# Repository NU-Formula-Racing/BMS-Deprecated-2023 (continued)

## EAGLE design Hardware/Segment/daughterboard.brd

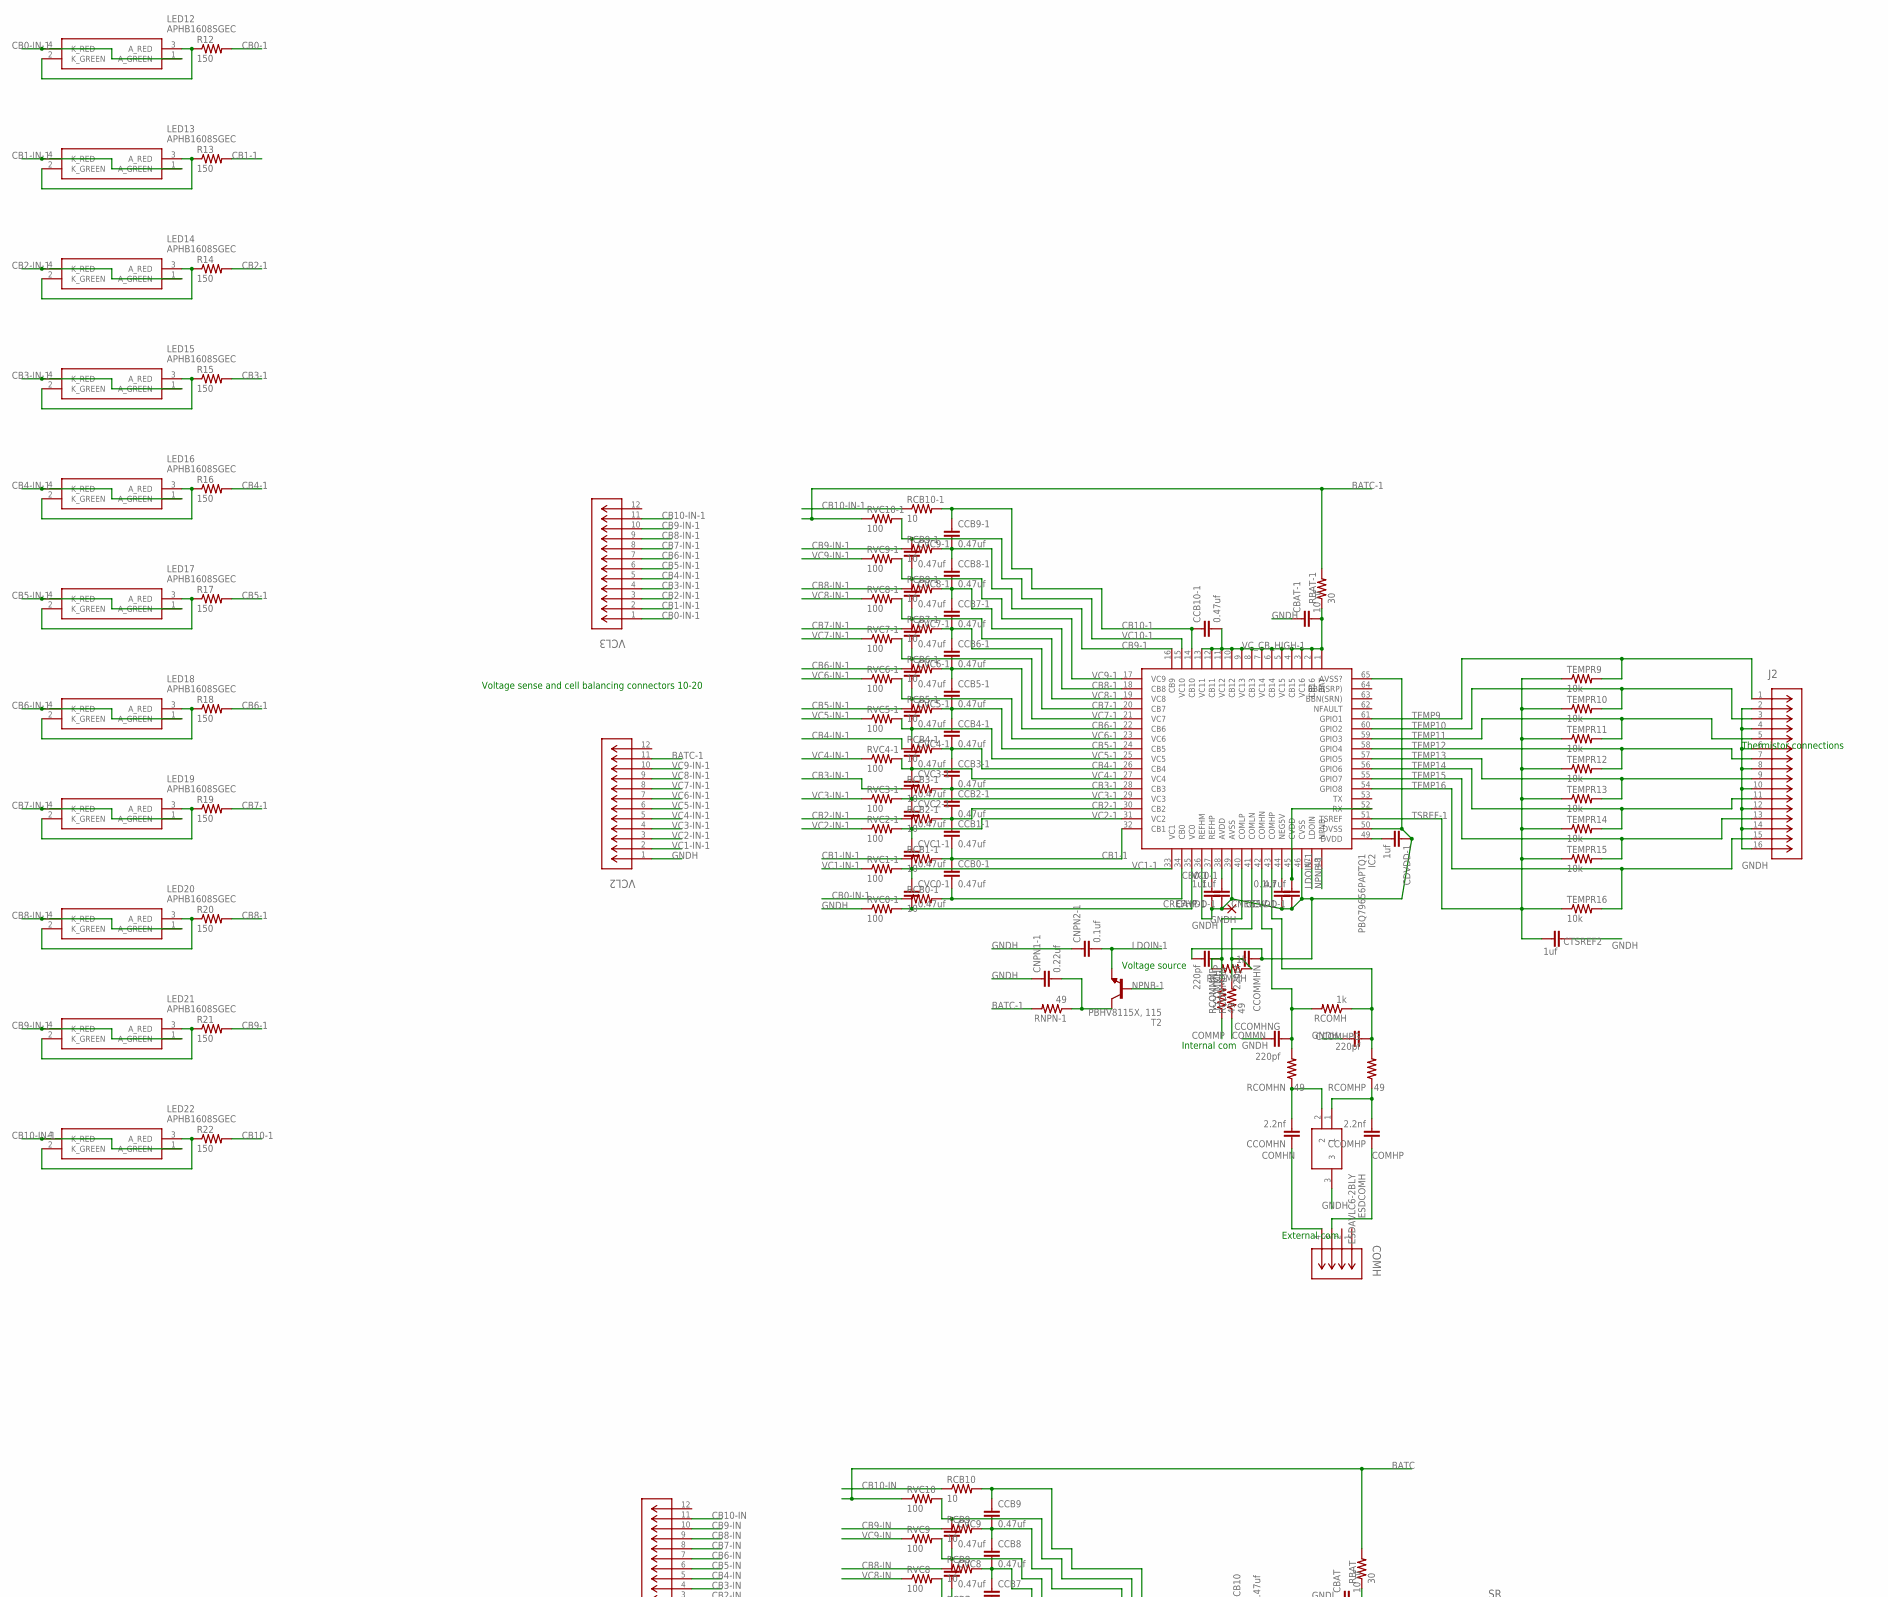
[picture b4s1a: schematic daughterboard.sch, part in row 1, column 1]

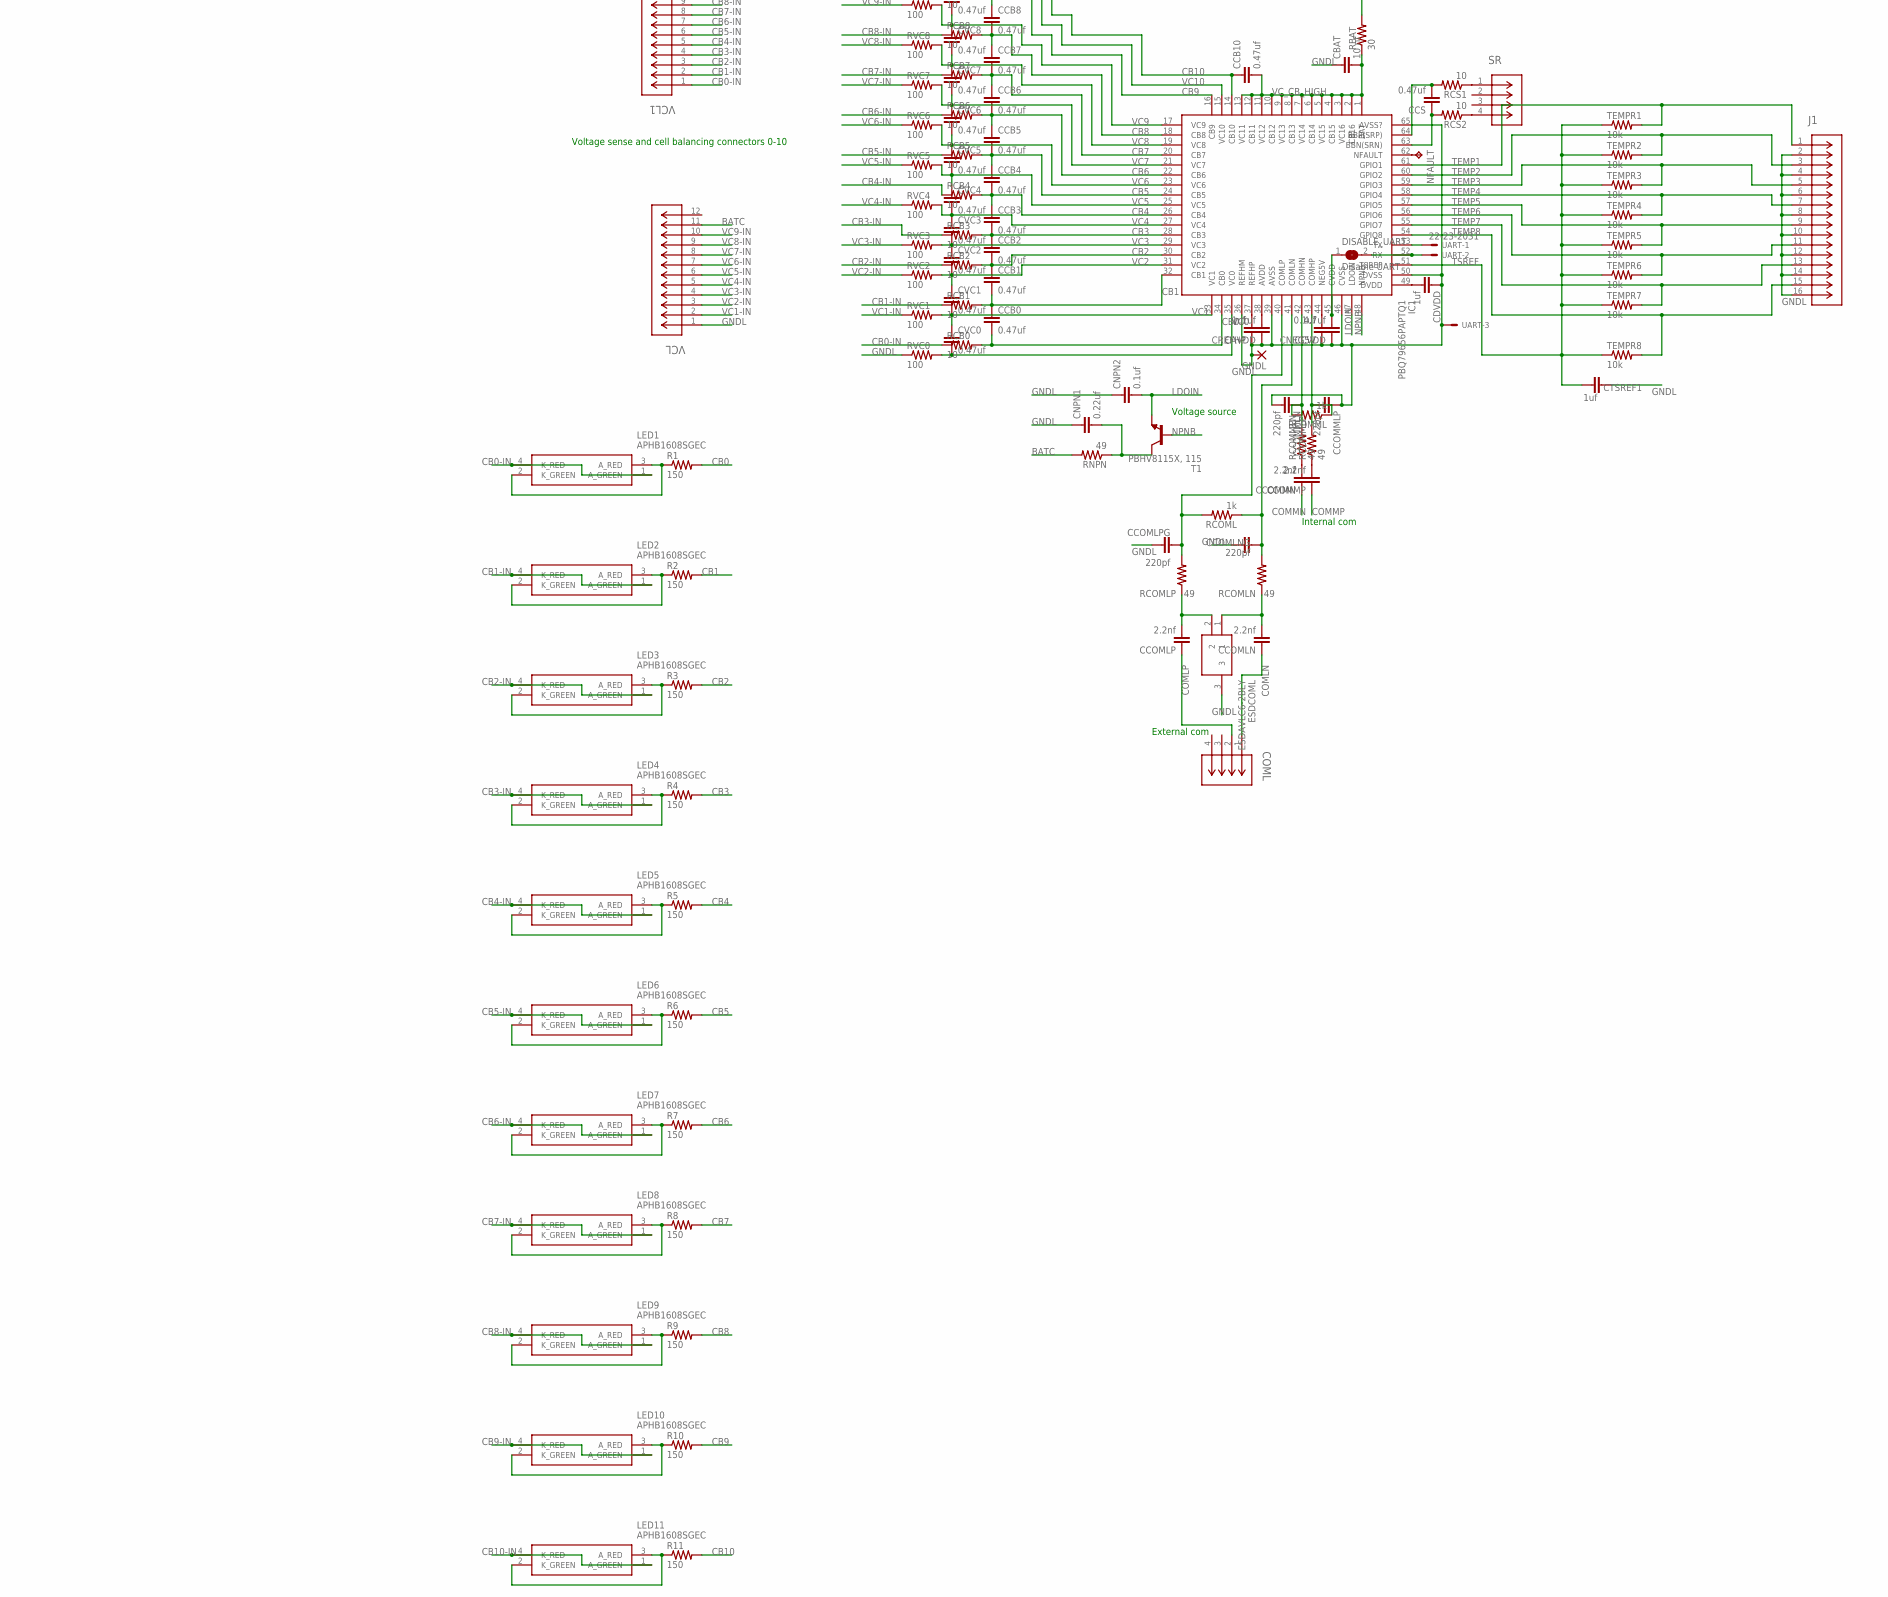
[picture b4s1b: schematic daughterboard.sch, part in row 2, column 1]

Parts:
CAVDD: 1uf; C0603
CAVDD-1: 1uf; C0603
CBAT: 10 nf; C0603
CBAT-1: 10 nf; C0603
CCB0, CCB0-1, CCB1, CCB1-1, CCB2, CCB2-1, CCB3, CCB3-1, CCB4, CCB4-1, CCB5, CCB5-1, CCB6, CCB6-1, CCB7, CCB7-1, CCB8, CCB8-1, CCB9, CCB9-1, CCB10, CCB10-1: 0.47uf; C0603
CCOMHN: 2.2nf; C0603
CCOMHNG: 220pf; C0603
CCOMHP: 2.2nf; C0603
CCOMHPG: 220pf; C0603
CCOMLN: 2.2nf; C0603
CCOMLNG: 220pf; C0603
CCOMLP: 2.2nf; C0603
CCOMLPG: 220pf; C0603
CCOMMHN: 220pf; C0603
CCOMMHP: 220pf; C0603
CCOMMLN: 220pf; C0603
CCOMMLP: 220pf; C0603
CCOMMN: 2.2nf; C0603
CCOMMP: 2.2nf; C0603
CCS: 0.47uf; C0603
CCVDD: 4.7uf; C0603
CCVDD-1: 4.7uf; C0603
CDVDD: 1uf; C0603
CDVDD-1: 1uf; C0603
CNEG5V, CNEG5V-1: 0.1uf; C0603
CNPN1, CNPN1-1: 0.22uf; C0603
CNPN2, CNPN2-1: 0.1uf; C0603
COMH: DF11-4DP-2DSA(24); CON4_2X2_UF_DF11_HIR
COML: DF11-4DP-2DSA(24); CON4_2X2_UF_DF11_HIR
CREFHP: 1uf; C0603
CREFHP-1: 1uf; C0603
CTSREF1, CTSREF2: 1uf; C0603
CVC0, CVC0-1, CVC1, CVC1-1, CVC2, CVC2-1, CVC3, CVC3-1, CVC4, CVC4-1, CVC5, CVC5-1, CVC6, CVC6-1, CVC7, CVC7-1, CVC8, CVC8-1, CVC9, CVC9-1: 0.47uf; C0603
DISABLE_UART: Disable UART; SJ
ESDCOMH: ESDAVLC6-2BLY; SOT95P255X150-3N
ESDCOML: ESDAVLC6-2BLY; SOT95P255X150-3N
GNDH: SMD5; SMD2,54-5,08
GNDL: SMD5; SMD2,54-5,08
IC1, IC2: PBQ79656PAPTQ1; QFP50P1200X1200X120-65N
J1, J2: DF11-16DP-2DSA(01); CONN_DF11-16DP-2DSA(01)_HIR
LED1, LED2, LED3, LED4, LED5, LED6, LED7, LED8, LED9, LED10, LED11, LED12, LED13, LED14, LED15, LED16, LED17, LED18, LED19, LED20, LED21, LED22: APHB1608SGEC
NFAULT: TPB2,54; B2,54
R1, R2, R3, R4, R5, R6, R7, R8, R9, R10, R11, R12, R13, R14, R15, R16, R17, R18, R19, R20, R21, R22: 150; R0603
RBAT: 30; R0603
RBAT-1: 30; R0603
RCB0, RCB0-1, RCB1, RCB1-1, RCB2, RCB2-1, RCB3, RCB3-1, RCB4, RCB4-1, RCB5, RCB5-1, RCB6, RCB6-1, RCB7, RCB7-1, RCB8, RCB8-1, RCB9, RCB9-1, RCB10, RCB10-1: 10; R1210
RCOMH: 1k; R0603
RCOMHN: 49; R0603
RCOMHP: 49; R0603
RCOML: 1k; R0603
RCOMLN: 49; R0603
RCOMLP: 49; R0603
RCOMMH: 1k; R0603
RCOMMHN: 49; R0603
RCOMMHP: 49; R0603
RCOMML: 1k; R0603
RCOMMLN: 49; R0603
RCOMMLP: 49; R0603
RCS1, RCS2: 10; R0603
RNPN: 49; R0603
RNPN-1: 49; R0603
RVC0, RVC0-1, RVC1, RVC1-1, RVC2, RVC2-1, RVC3, RVC3-1, RVC4, RVC4-1, RVC5, RVC5-1, RVC6, RVC6-1, RVC7, RVC7-1, RVC8, RVC8-1, RVC9, RVC9-1, RVC10, RVC10-1: 100; R0603
SR: DF11-4DP-2DSA(24); CON4_2X2_UF_DF11_HIR
T1, T2: PBHV8115X, 115; SOT89-BCE
TEMPR1, TEMPR2, TEMPR3, TEMPR4, TEMPR5, TEMPR6, TEMPR7, TEMPR8, TEMPR9, TEMPR10, TEMPR11, TEMPR12, TEMPR13, TEMPR14, TEMPR15, TEMPR16: 10k; R0603
UART: 22-23-2031
VCL, VCL1, VCL2, VCL3: DF11-12DP-2DSA(01); CON12_2X6_UF_DF11_HIR

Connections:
BATC: RBAT.2, RNPN.2, RVC10.1, VCL.11
BATC-1: RBAT-1.2, RNPN-1.2, RVC10-1.1, VCL2.11
CB0: CCB0.2, IC1.34 (CB0), R1.2, RCB0.2
CB0-1: CCB0-1.2, IC2.34 (CB0), R12.2, RCB0-1.2
CB0-IN: LED1.1 (A_GREEN), LED1.4 (K_RED), RCB0.1, VCL1.1
CB0-IN-1: LED12.1 (A_GREEN), LED12.4 (K_RED), RCB0-1.1, VCL3.1
CB1: CCB0.1, CCB1.2, IC1.32 (CB1), R2.2, RCB1.2
CB1-1: CCB0-1.1, CCB1-1.2, IC2.32 (CB1), R13.2, RCB1-1.2
CB1-IN: LED2.1 (A_GREEN), LED2.4 (K_RED), RCB1.1, VCL1.2
CB1-IN-1: LED13.1 (A_GREEN), LED13.4 (K_RED), RCB1-1.1, VCL3.2
CB2: CCB1.1, CCB2.2, IC1.30 (CB2), R3.2, RCB2.2
CB2-1: CCB1-1.1, CCB2-1.2, IC2.30 (CB2), R14.2, RCB2-1.2
CB2-IN: LED3.1 (A_GREEN), LED3.4 (K_RED), RCB2.1, VCL1.3
CB2-IN-1: LED14.1 (A_GREEN), LED14.4 (K_RED), RCB2-1.1, VCL3.3
CB3: CCB2.1, CCB3.2, IC1.28 (CB3), R4.2, RCB3.2
CB3-1: CCB2-1.1, CCB3-1.2, IC2.28 (CB3), R15.2, RCB3-1.2
CB3-IN: LED4.1 (A_GREEN), LED4.4 (K_RED), RCB3.1, VCL1.4
CB3-IN-1: LED15.1 (A_GREEN), LED15.4 (K_RED), RCB3-1.1, VCL3.4
CB4: CCB3.1, CCB4.2, IC1.26 (CB4), R5.2, RCB4.2
CB4-1: CCB3-1.1, CCB4-1.2, IC2.26 (CB4), R16.2, RCB4-1.2
CB4-IN: LED5.1 (A_GREEN), LED5.4 (K_RED), RCB4.1, VCL1.5
CB4-IN-1: LED16.1 (A_GREEN), LED16.4 (K_RED), RCB4-1.1, VCL3.5
CB5: CCB4.1, CCB5.2, IC1.24 (CB5), R6.2, RCB5.2
CB5-1: CCB4-1.1, CCB5-1.2, IC2.24 (CB5), R17.2, RCB5-1.2
CB5-IN: LED6.1 (A_GREEN), LED6.4 (K_RED), RCB5.1, VCL1.6
CB5-IN-1: LED17.1 (A_GREEN), LED17.4 (K_RED), RCB5-1.1, VCL3.6
CB6: CCB5.1, CCB6.2, IC1.22 (CB6), R7.2, RCB6.2
CB6-1: CCB5-1.1, CCB6-1.2, IC2.22 (CB6), R18.2, RCB6-1.2
CB6-IN: LED7.1 (A_GREEN), LED7.4 (K_RED), RCB6.1, VCL1.7
CB6-IN-1: LED18.1 (A_GREEN), LED18.4 (K_RED), RCB6-1.1, VCL3.7
CB7: CCB6.1, CCB7.2, IC1.20 (CB7), R8.2, RCB7.2
CB7-1: CCB6-1.1, CCB7-1.2, IC2.20 (CB7), R19.2, RCB7-1.2
CB7-IN: LED8.1 (A_GREEN), LED8.4 (K_RED), RCB7.1, VCL1.8
CB7-IN-1: LED19.1 (A_GREEN), LED19.4 (K_RED), RCB7-1.1, VCL3.8
CB8: CCB7.1, CCB8.2, IC1.18 (CB8), R9.2, RCB8.2
CB8-1: CCB7-1.1, CCB8-1.2, IC2.18 (CB8), R20.2, RCB8-1.2
CB8-IN: LED9.1 (A_GREEN), LED9.4 (K_RED), RCB8.1, VCL1.9
CB8-IN-1: LED20.1 (A_GREEN), LED20.4 (K_RED), RCB8-1.1, VCL3.9
CB9: CCB8.1, CCB9.2, IC1.16 (CB9), R10.2, RCB9.2
CB9-1: CCB8-1.1, CCB9-1.2, IC2.16 (CB9), R21.2, RCB9-1.2
CB9-IN: LED10.1 (A_GREEN), LED10.4 (K_RED), RCB9.1, VCL1.10
CB9-IN-1: LED21.1 (A_GREEN), LED21.4 (K_RED), RCB9-1.1, VCL3.10
CB10: CCB9.1, CCB10.1, IC1.14 (CB10), R11.2, RCB10.2
CB10-1: CCB9-1.1, CCB10-1.1, IC2.14 (CB10), R22.2, RCB10-1.2
CB10-IN: LED11.1 (A_GREEN), LED11.4 (K_RED), RCB10.1, VCL1.11
CB10-IN-1: LED22.1 (A_GREEN), LED22.4 (K_RED), RCB10-1.1, VCL3.11
COMHN: CCOMHN.1, COMH.4
COMHP: CCOMHP.1, COMH.3
COMLN: CCOMLN.1, COML.1
COMLP: CCOMLP.1, COML.2
COMMN: CCOMMN.1, RCOMMHN.1
COMMP: CCOMMP.1, RCOMMHP.1
CVDD: CCVDD.2, DISABLE_UART.1, IC1.45 (CVDD)
CVDD-1: CCVDD-1.2, IC2.45 (CVDD), IC2.52 (RX)
GNDH: CAVDD-1.1, CBAT-1.1, CCOMHNG.1, CCOMHPG.1, CCOMMHN.1, CCOMMHP.2, CCVDD-1.1, CDVDD-1.1, CNEG5V-1.1, CNPN1-1.1, CNPN2-1.1, CREFHP-1.1, CTSREF2.1, ESDCOMH.3, GNDH.1, IC2.36 (REFHM), IC2.39 (AVSS), IC2.46 (CVSS), IC2.50 (DVSS), IC2.65 (AVSS?), J2.2, J2.4, J2.6, J2.8, J2.10, J2.12, J2.14, J2.16, RVC0-1.1, VCL2.1
GNDL: CAVDD.1, CBAT.1, CCOMLNG.1, CCOMLPG.1, CCOMMLN.2, CCOMMLP.1, CCVDD.1, CDVDD.1, CNEG5V.1, CNPN1.1, CNPN2.1, CREFHP.1, CTSREF1.1, ESDCOML.3, GNDL.1, IC1.36 (REFHM), IC1.39 (AVSS), IC1.46 (CVSS), IC1.50 (DVSS), IC1.65 (AVSS?), J1.2, J1.4, J1.6, J1.8, J1.10, J1.12, J1.14, J1.16, RVC0.1, UART.3, VCL.1
LDOIN: CNPN2.2, IC1.47 (LDOIN), T1.E
LDOIN-1: CNPN2-1.2, IC2.47 (LDOIN), T2.E
unnamed: CCOMHP.2, ESDCOMH.1, RCOMHP.1
unnamed: CCOMHN.2, ESDCOMH.2, RCOMHN.1
unnamed: DISABLE_UART.2, IC1.52 (RX), UART.2
unnamed: CCS.2, IC1.64 (BBP(SRP)), RCS1.2
unnamed: LED12.2 (K_GREEN), LED12.3 (A_RED), R12.1
unnamed: LED2.2 (K_GREEN), LED2.3 (A_RED), R2.1
unnamed: CCS.1, IC1.63 (BBN(SRN)), RCS2.2
unnamed: LED13.2 (K_GREEN), LED13.3 (A_RED), R13.1
unnamed: IC1.53 (TX), UART.1
unnamed: IC1.62 (NFAULT), NFAULT.TP
unnamed: LED14.2 (K_GREEN), LED14.3 (A_RED), R14.1
unnamed: LED3.2 (K_GREEN), LED3.3 (A_RED), R3.1
unnamed: RCS1.1, SR.1
unnamed: LED15.2 (K_GREEN), LED15.3 (A_RED), R15.1
unnamed: LED16.2 (K_GREEN), LED16.3 (A_RED), R16.1
unnamed: RCS2.1, SR.4
unnamed: LED17.2 (K_GREEN), LED17.3 (A_RED), R17.1
unnamed: LED4.2 (K_GREEN), LED4.3 (A_RED), R4.1
unnamed: LED18.2 (K_GREEN), LED18.3 (A_RED), R18.1
unnamed: LED19.2 (K_GREEN), LED19.3 (A_RED), R19.1
unnamed: LED5.2 (K_GREEN), LED5.3 (A_RED), R5.1
unnamed: LED20.2 (K_GREEN), LED20.3 (A_RED), R20.1
unnamed: LED21.2 (K_GREEN), LED21.3 (A_RED), R21.1
unnamed: LED6.2 (K_GREEN), LED6.3 (A_RED), R6.1
unnamed: LED22.2 (K_GREEN), LED22.3 (A_RED), R22.1
unnamed: LED7.2 (K_GREEN), LED7.3 (A_RED), R7.1
unnamed: CCOMLNG.2, IC1.41 (COMLN), RCOML.1, RCOMLN.2
unnamed: LED8.2 (K_GREEN), LED8.3 (A_RED), R8.1
unnamed: CREFHP.2, IC1.37 (REFHP)
unnamed: LED9.2 (K_GREEN), LED9.3 (A_RED), R9.1
unnamed: LED10.2 (K_GREEN), LED10.3 (A_RED), R10.1
unnamed: LED11.2 (K_GREEN), LED11.3 (A_RED), R11.1
unnamed: LED1.2 (K_GREEN), LED1.3 (A_RED), R1.1
unnamed: CAVDD.2, IC1.38 (AVDD)
unnamed: CNEG5V.2, IC1.44 (NEG5V)
unnamed: CCOMLPG.2, IC1.40 (COMLP), RCOML.2, RCOMLP.2
unnamed: CDVDD.2, IC1.49 (DVDD)
unnamed: CCOMMLN.1, IC1.42 (COMHN), RCOMML.2, RCOMMLN.2
unnamed: CCOMMLP.2, IC1.43 (COMHP), RCOMML.1, RCOMMLP.2
unnamed: CCOMMN.2, RCOMMLN.1
unnamed: CCOMMP.2, RCOMMLP.1
unnamed: CNPN1.2, RNPN.1, T1.C
unnamed: CCOMLP.2, ESDCOML.2, RCOMLP.1
unnamed: CCOMLN.2, ESDCOML.1, RCOMLN.1
unnamed: CREFHP-1.2, IC2.37 (REFHP)
unnamed: CAVDD-1.2, IC2.38 (AVDD)
unnamed: CNEG5V-1.2, IC2.44 (NEG5V)
unnamed: CDVDD-1.2, IC2.49 (DVDD)
unnamed: CCOMMHN.2, IC2.41 (COMLN), RCOMMH.1, RCOMMHN.2
unnamed: CCOMMHP.1, IC2.40 (COMLP), RCOMMH.2, RCOMMHP.2
unnamed: CNPN1-1.2, RNPN-1.1, T2.C
unnamed: CCOMHPG.2, IC2.43 (COMHP), RCOMH.1, RCOMHP.2
unnamed: CCOMHNG.2, IC2.42 (COMHN), RCOMH.2, RCOMHN.2
NPNB: IC1.48 (NPNB), T1.B
NPNB-1: IC2.48 (NPNB), T2.B
TEMP1: IC1.61 (GPIO1), J1.1, TEMPR1.2
TEMP2: IC1.60 (GPIO2), J1.3, TEMPR2.2
TEMP3: IC1.59 (GPIO3), J1.5, TEMPR3.2
TEMP4: IC1.58 (GPIO4), J1.7, TEMPR4.2
TEMP5: IC1.57 (GPIO5), J1.9, TEMPR5.2
TEMP6: IC1.56 (GPIO6), J1.11, TEMPR6.2
TEMP7: IC1.55 (GPIO7), J1.13, TEMPR7.2
TEMP8: IC1.54 (GPIO8), J1.15, TEMPR8.2
TEMP9: IC2.61 (GPIO1), J2.1, TEMPR9.2
TEMP10: IC2.60 (GPIO2), J2.3, TEMPR10.2
TEMP11: IC2.59 (GPIO3), J2.5, TEMPR11.2
TEMP12: IC2.58 (GPIO4), J2.7, TEMPR12.2
TEMP13: IC2.57 (GPIO5), J2.9, TEMPR13.2
TEMP14: IC2.56 (GPIO6), J2.11, TEMPR14.2
TEMP15: IC2.55 (GPIO7), J2.13, TEMPR15.2
TEMP16: IC2.54 (GPIO8), J2.15, TEMPR16.2
TSREF: CTSREF1.2, IC1.51 (TSREF), TEMPR1.1, TEMPR2.1, TEMPR3.1, TEMPR4.1, TEMPR5.1, TEMPR6.1, TEMPR7.1, TEMPR8.1
TSREF-1: CTSREF2.2, IC2.51 (TSREF), TEMPR9.1, TEMPR10.1, TEMPR11.1, TEMPR12.1, TEMPR13.1, TEMPR14.1, TEMPR15.1, TEMPR16.1
VC0: CVC0.2, IC1.35 (VC0), RVC0.2
VC0-1: CVC0-1.2, IC2.35 (VC0), RVC0-1.2
VC1: CVC0.1, CVC1.2, IC1.33 (VC1), RVC1.2
VC1-1: CVC0-1.1, CVC1-1.2, IC2.33 (VC1), RVC1-1.2
VC1-IN: RVC1.1, VCL.2
VC1-IN-1: RVC1-1.1, VCL2.2
VC2: CVC1.1, CVC2.2, IC1.31 (VC2), RVC2.2
VC2-1: CVC1-1.1, CVC2-1.2, IC2.31 (VC2), RVC2-1.2
VC2-IN: RVC2.1, VCL.3
VC2-IN-1: RVC2-1.1, VCL2.3
VC3: CVC2.1, CVC3.2, IC1.29 (VC3), RVC3.2
VC3-1: CVC2-1.1, CVC3-1.2, IC2.29 (VC3), RVC3-1.2
VC3-IN: RVC3.1, VCL.4
VC3-IN-1: RVC3-1.1, VCL2.4
VC4: CVC3.1, CVC4.2, IC1.27 (VC4), RVC4.2
VC4-1: CVC3-1.1, CVC4-1.2, IC2.27 (VC4), RVC4-1.2
VC4-IN: RVC4.1, VCL.5
VC4-IN-1: RVC4-1.1, VCL2.5
VC5: CVC4.1, CVC5.2, IC1.25 (VC5), RVC5.2
VC5-1: CVC4-1.1, CVC5-1.2, IC2.25 (VC5), RVC5-1.2
VC5-IN: RVC5.1, VCL.6
VC5-IN-1: RVC5-1.1, VCL2.6
VC6: CVC5.1, CVC6.2, IC1.23 (VC6), RVC6.2
VC6-1: CVC5-1.1, CVC6-1.2, IC2.23 (VC6), RVC6-1.2
VC6-IN: RVC6.1, VCL.7
VC6-IN-1: RVC6-1.1, VCL2.7
VC7: CVC6.1, CVC7.2, IC1.21 (VC7), RVC7.2
VC7-1: CVC6-1.1, CVC7-1.2, IC2.21 (VC7), RVC7-1.2
VC7-IN: RVC7.1, VCL.8
VC7-IN-1: RVC7-1.1, VCL2.8
VC8: CVC7.1, CVC8.2, IC1.19 (VC8), RVC8.2
VC8-1: CVC7-1.1, CVC8-1.2, IC2.19 (VC8), RVC8-1.2
VC8-IN: RVC8.1, VCL.9
VC8-IN-1: RVC8-1.1, VCL2.9
VC9: CVC8.1, CVC9.2, IC1.17 (VC9), RVC9.2
VC9-1: CVC8-1.1, CVC9-1.2, IC2.17 (VC9), RVC9-1.2
VC9-IN: RVC9.1, VCL.10
VC9-IN-1: RVC9-1.1, VCL2.10
VC10: CVC9.1, IC1.15 (VC10), RVC10.2
VC10-1: CVC9-1.1, IC2.15 (VC10), RVC10-1.2
VC_CB_HIGH: CBAT.2, CCB10.2, IC1.1 (BAT), IC1.2 (CB16), IC1.3 (VC16), IC1.4 (CB15), IC1.5 (VC15), IC1.6 (CB14), IC1.7 (VC14), IC1.8 (CB13), IC1.9 (VC13), IC1.10 (CB12), IC1.11 (VC12), IC1.12 (CB11), IC1.13 (VC11), RBAT.1
VC_CB_HIGH-1: CBAT-1.2, CCB10-1.2, IC2.1 (BAT), IC2.2 (CB16), IC2.3 (VC16), IC2.4 (CB15), IC2.5 (VC15), IC2.6 (CB14), IC2.7 (VC14), IC2.8 (CB13), IC2.9 (VC13), IC2.10 (CB12), IC2.11 (VC12), IC2.12 (CB11), IC2.13 (VC11), RBAT-1.1

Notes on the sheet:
Voltage sense and cell balancing connectors 0-10
Voltage sense and cell balancing connectors 10-20
External com
Internal com
Voltage source
Thermistor connections

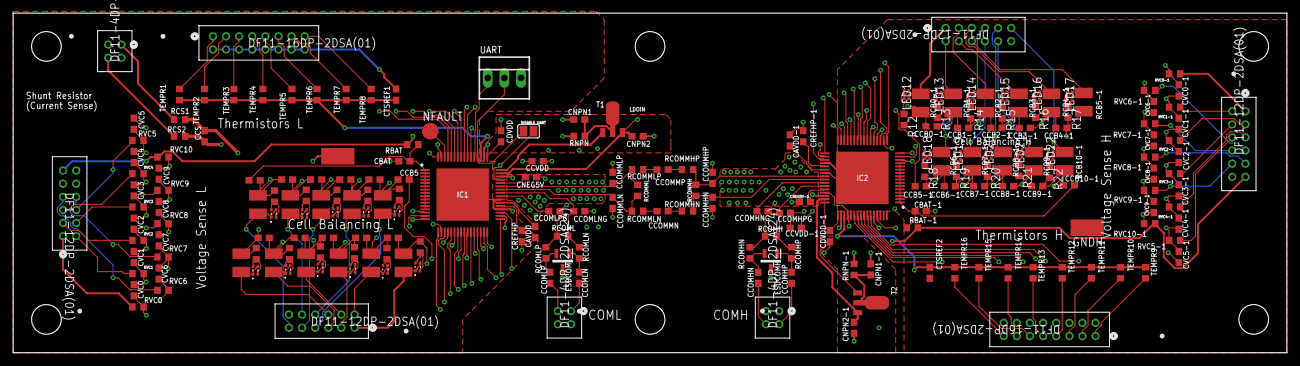
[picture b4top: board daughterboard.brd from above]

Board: 4 copper layers, 194.3 x 51.8 mm, 217 parts (0 on the bottom side), 173 nets.

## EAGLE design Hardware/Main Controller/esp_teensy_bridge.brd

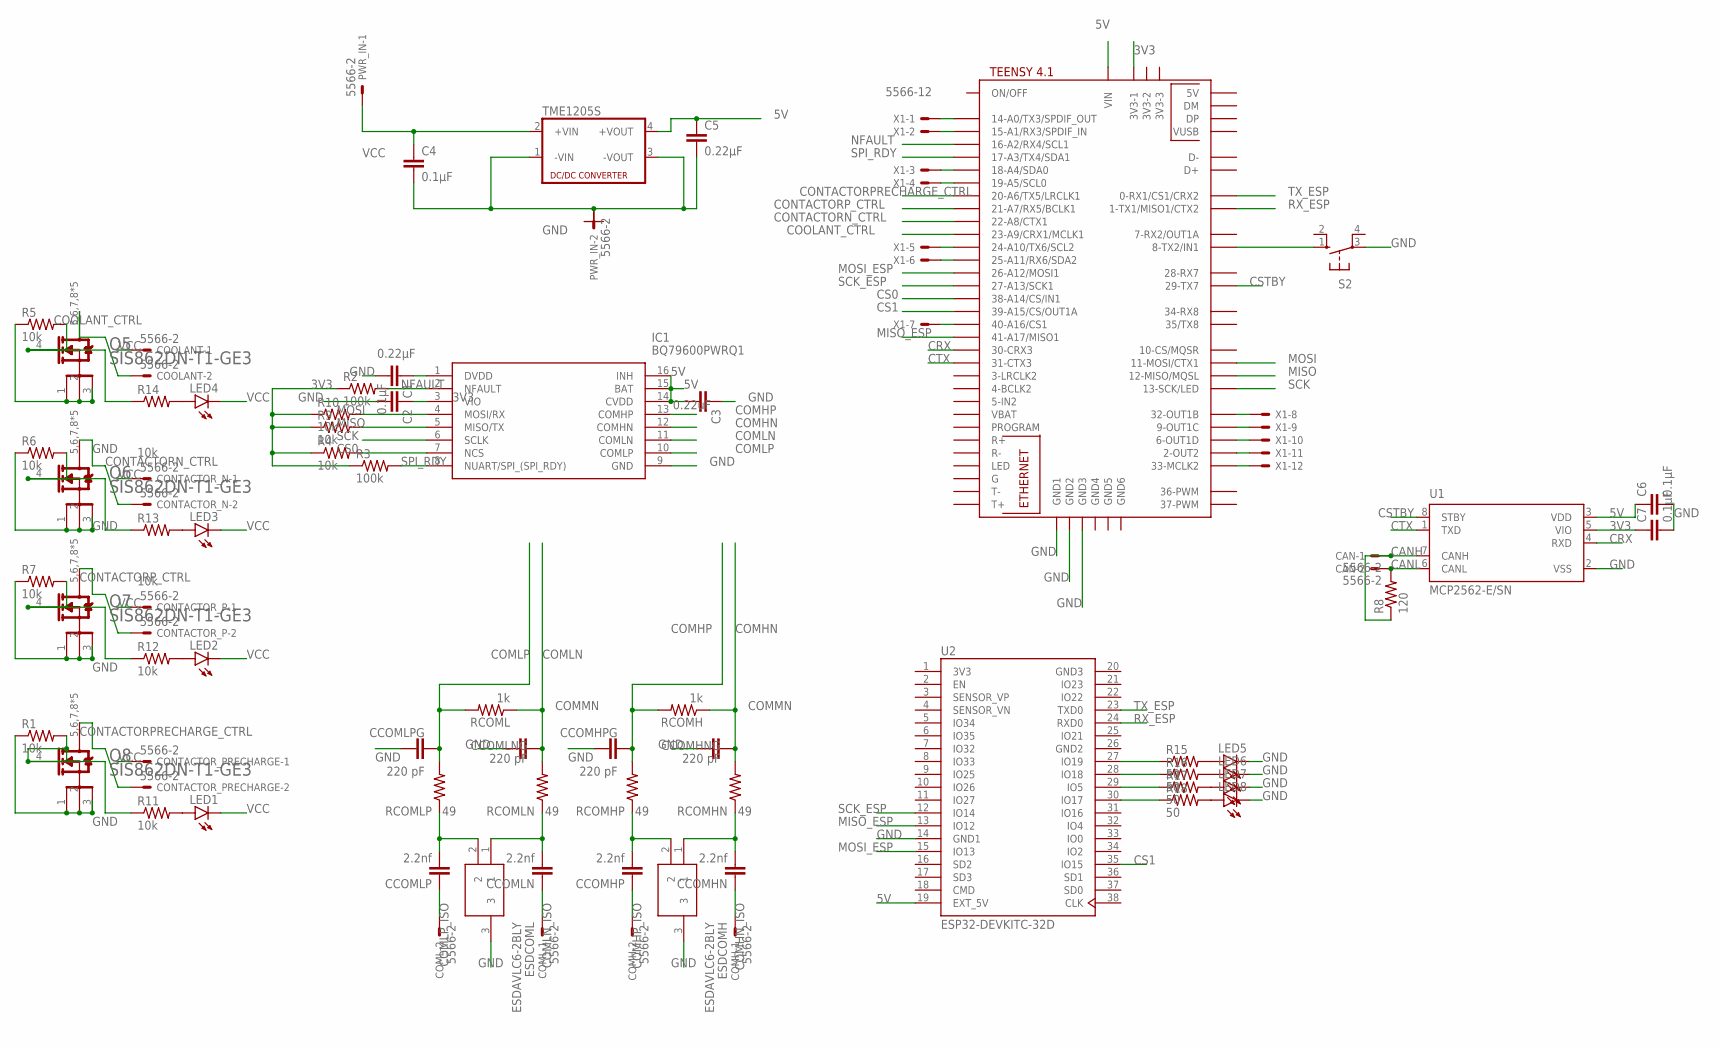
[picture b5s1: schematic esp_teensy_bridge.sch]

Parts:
C1, C5: 0.22μF; C0603
C2, C4, C6, C7: 0.1μF; C0603
C3: 0.22uF; C0603
CAN: 5566-2
CCOMHN: 2.2nf; C0603
CCOMHNG: 220 pF; C0603
CCOMHP: 2.2nf; C0603
CCOMHPG: 220 pF; C0603
CCOMLN: 2.2nf; C0603
CCOMLNG: 220 pF; C0603
CCOMLP: 2.2nf; C0603
CCOMLPG: 220 pF; C0603
COMH: 5566-2
COML: 5566-2
CONTACTOR_N: 5566-2
CONTACTOR_P: 5566-2
CONTACTOR_PRECHARGE: 5566-2
COOLANT: 5566-2
ESDCOMH: ESDAVLC6-2BLY; SOT95P255X150-3N
ESDCOML: ESDAVLC6-2BLY; SOT95P255X150-3N
IC1: BQ79600PWRQ1; SOP65P640X120-16N
LED1, LED2, LED3, LED4, LED5, LED6, LED7, LED8: LEDSML0603; SML0603
PWR_IN: 5566-2
Q5, Q6, Q7, Q8: VISHAY_SIS862DN-T1-GE3VISHAY_SIS862DN-T1-GE3_0_0; VISHAY_SIS862DN-T1-GE3_0
R1, R4, R5, R6, R7, R9, R10, R11, R12, R13, R14: 10k; R0603
R2, R3: 100k; R0603
R8: 120; R0603
R15, R16, R17, R18: 50; R0603
RCOMH: 1k; R0603
RCOMHN: 49; R0603
RCOMHP: 49; R0603
RCOML: 1k; R0603
RCOMLN: 49; R0603
RCOMLP: 49; R0603
S2: 10-XX; B3F-10XX
TME1205S: NME
U1: MCP2562-E/SN; SOIC127P600X175-8N
U2: ESP32-DEVKITC-32D; MODULE_ESP32-DEVKITC-32D
U$3: TEENSY41
X1: 5566-12

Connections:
3V3: C2.1, C7.1, IC1.3 (VIO), R2.1, R3.1, R4.1, R9.1, R10.1, U1.5 (VIO), U2.1 (3V3), U$3.3V3-1
5V: C3.2, C5.1, C6.1, IC1.14 (CVDD), IC1.15 (BAT), IC1.16 (INH), TME1205S.4 (+VOUT), U1.3 (VDD), U2.19 (EXT_5V), U$3.VIN
CANH: CAN.1, R8.1, U1.7 (CANH)
CANL: CAN.2, R8.2, U1.6 (CANL)
COMHN: CCOMHNG.2, IC1.12 (COMHN), RCOMH.1, RCOMHN.2
COMHN_ISO: CCOMHN.1, COMH.1
COMHP: CCOMHPG.2, IC1.13 (COMHP), RCOMH.2, RCOMHP.2
COMHP_ISO: CCOMHP.1, COMH.2
COMLN: CCOMLNG.2, IC1.11 (COMLN), RCOML.1, RCOMLN.2
COMLN_ISO: CCOMLN.1, COML.1
COMLP: CCOMLPG.2, IC1.10 (COMLP), RCOML.2, RCOMLP.2
COMLP_ISO: CCOMLP.1, COML.2
CONTACTORN_CTRL: Q6.4 (G), R6.2, R13.1, U$3.22-A8/CTX1
CONTACTORPRECHARGE_CTRL: Q8.4 (G), R1.2, R11.1, U$3.20-A6/TX5/LRCLK1
CONTACTORP_CTRL: Q7.4 (G), R7.2, R12.1, U$3.21-A7/RX5/BCLK1
COOLANT_CTRL: Q5.4 (G), R5.2, R14.1, U$3.23-A9/CRX1/MCLK1
CRX: U1.4 (RXD), U$3.30-CRX3
CS0: IC1.7 (NCS), R4.2, U$3.38-A14/CS/IN1
CS1: U2.35 (IO15), U$3.39-A15/CS/OUT1A
CSTBY: U1.8 (STBY), U$3.29-TX7
CTX: U1.1 (TXD), U$3.31-CTX3
GND: C1.2, C2.2, C3.1, C4.2, C5.2, C6.2, C7.2, CCOMHNG.1, CCOMHPG.1, CCOMLNG.1, CCOMLPG.1, ESDCOMH.3, ESDCOML.3, IC1.9 (GND), LED5.C, LED6.C, LED7.C, LED8.C, PWR_IN.2, Q5.1 (1_S), Q5.2 (2_S), Q5.3 (3_S), Q6.1 (1_S), Q6.2 (2_S), Q6.3 (3_S), Q7.1 (1_S), Q7.2 (2_S), Q7.3 (3_S), Q8.1 (1_S), Q8.2 (2_S), Q8.3 (3_S), R1.1, R5.1, R6.1, R7.1, S2.3, TME1205S.1 (-VIN), TME1205S.3 (-VOUT), U1.2 (VSS), U2.14 (GND1), U$3.GND1, U$3.GND2, U$3.GND3
GND2: U2.26 (GND2)
GND3: U2.20 (GND3)
MISO: IC1.5 (MISO/TX), R9.2, U$3.12-MISO/MQSL
MISO_ESP: U2.13 (IO12), U$3.41-A17/MISO1
MOSI: IC1.4 (MOSI/RX), R10.2, U$3.11-MOSI/CTX1
MOSI_ESP: U2.15 (IO13), U$3.26-A12/MOSI1
unnamed: C1.1, IC1.1 (DVDD)
unnamed: CONTACTOR_N.2, Q6.5,6,7,8 (D), Q6.5,6,7,8-2 (D), Q6.5,6,7,8-3 (D), Q6.5,6,7,8-4 (D), Q6.5,6,7,8-5 (D)
unnamed: LED1.A, R11.2
unnamed: LED2.A, R12.2
unnamed: COOLANT.2, Q5.5,6,7,8 (D), Q5.5,6,7,8-2 (D), Q5.5,6,7,8-3 (D), Q5.5,6,7,8-4 (D), Q5.5,6,7,8-5 (D)
unnamed: CONTACTOR_PRECHARGE.2, Q8.5,6,7,8 (D), Q8.5,6,7,8-2 (D), Q8.5,6,7,8-3 (D), Q8.5,6,7,8-4 (D), Q8.5,6,7,8-5 (D)
unnamed: S2.1 (S), U$3.8-TX2/IN1
unnamed: LED3.A, R13.2
unnamed: CCOMLP.2, ESDCOML.2, RCOMLP.1
unnamed: CCOMLN.2, ESDCOML.1, RCOMLN.1
unnamed: CONTACTOR_P.2, Q7.5,6,7,8 (D), Q7.5,6,7,8-2 (D), Q7.5,6,7,8-3 (D), Q7.5,6,7,8-4 (D), Q7.5,6,7,8-5 (D)
unnamed: LED4.A, R14.2
unnamed: U$3.14-A0/TX3/SPDIF_OUT, X1.1
unnamed: CCOMHP.2, ESDCOMH.2, RCOMHP.1
unnamed: CCOMHN.2, ESDCOMH.1, RCOMHN.1
unnamed: U$3.15-A1/RX3/SPDIF_IN, X1.2
unnamed: U$3.18-A4/SDA0, X1.3
unnamed: U$3.19-A5/SCL0, X1.4
unnamed: U$3.24-A10/TX6/SCL2, X1.5
unnamed: U$3.25-A11/RX6/SDA2, X1.6
unnamed: U$3.40-A16/CS1, X1.7
unnamed: U$3.32-OUT1B, X1.8
unnamed: U$3.9-OUT1C, X1.9
unnamed: U$3.6-OUT1D, X1.10
unnamed: U$3.33-MCLK2, X1.12
unnamed: U$3.2-OUT2, X1.11
unnamed: R15.1, U2.27 (IO19)
unnamed: R16.1, U2.28 (IO18)
unnamed: R17.1, U2.29 (IO5)
unnamed: R18.1, U2.30 (IO17)
unnamed: LED5.A, R15.2
unnamed: LED6.A, R16.2
unnamed: LED7.A, R17.2
unnamed: LED8.A, R18.2
NFAULT: IC1.2 (NFAULT), R2.2, U$3.16-A2/RX4/SCL1
RX_ESP: U2.24 (RXD0), U$3.1-TX1/MISO1/CTX2
SCK: IC1.6 (SCLK), U$3.13-SCK/LED
SCK_ESP: U2.12 (IO14), U$3.27-A13/SCK1
SPI_RDY: IC1.8 (NUART/SPI_(SPI_RDY)), R3.2, U$3.17-A3/TX4/SDA1
TX_ESP: U2.23 (TXD0), U$3.0-RX1/CS1/CRX2
VCC: C4.1, CONTACTOR_N.1, CONTACTOR_P.1, CONTACTOR_PRECHARGE.1, COOLANT.1, LED1.C, LED2.C, LED3.C, LED4.C, PWR_IN.1, TME1205S.2 (+VIN)

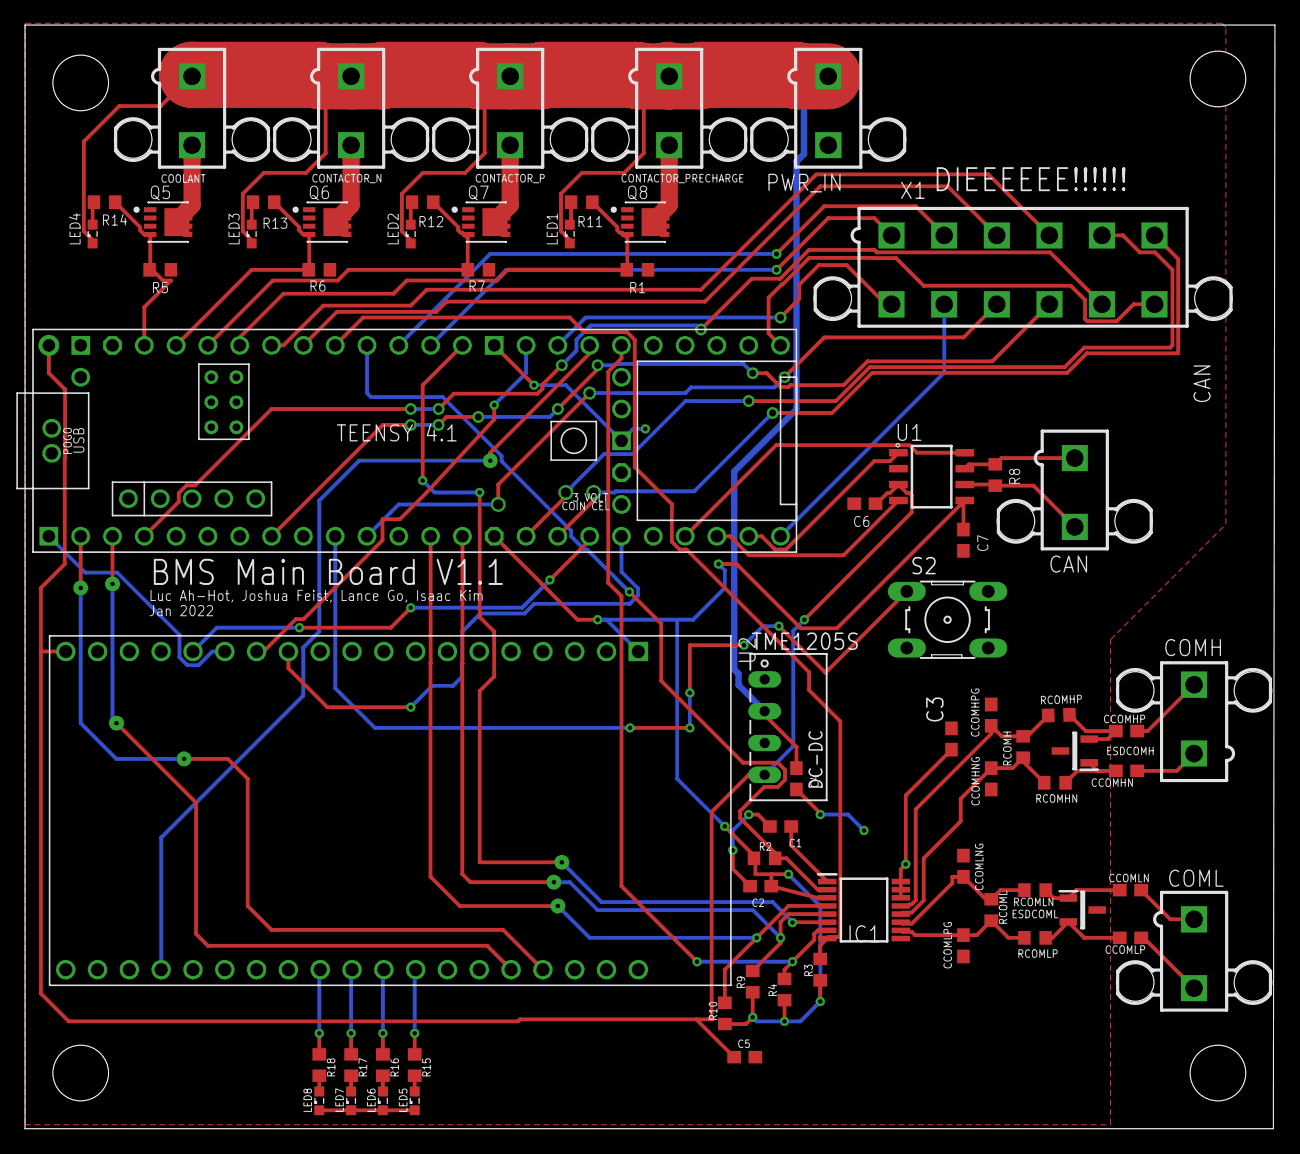
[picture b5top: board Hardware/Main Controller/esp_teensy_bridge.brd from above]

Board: 2 copper layers, 99.8 x 88.1 mm, 68 parts (0 on the bottom side), 67 nets.

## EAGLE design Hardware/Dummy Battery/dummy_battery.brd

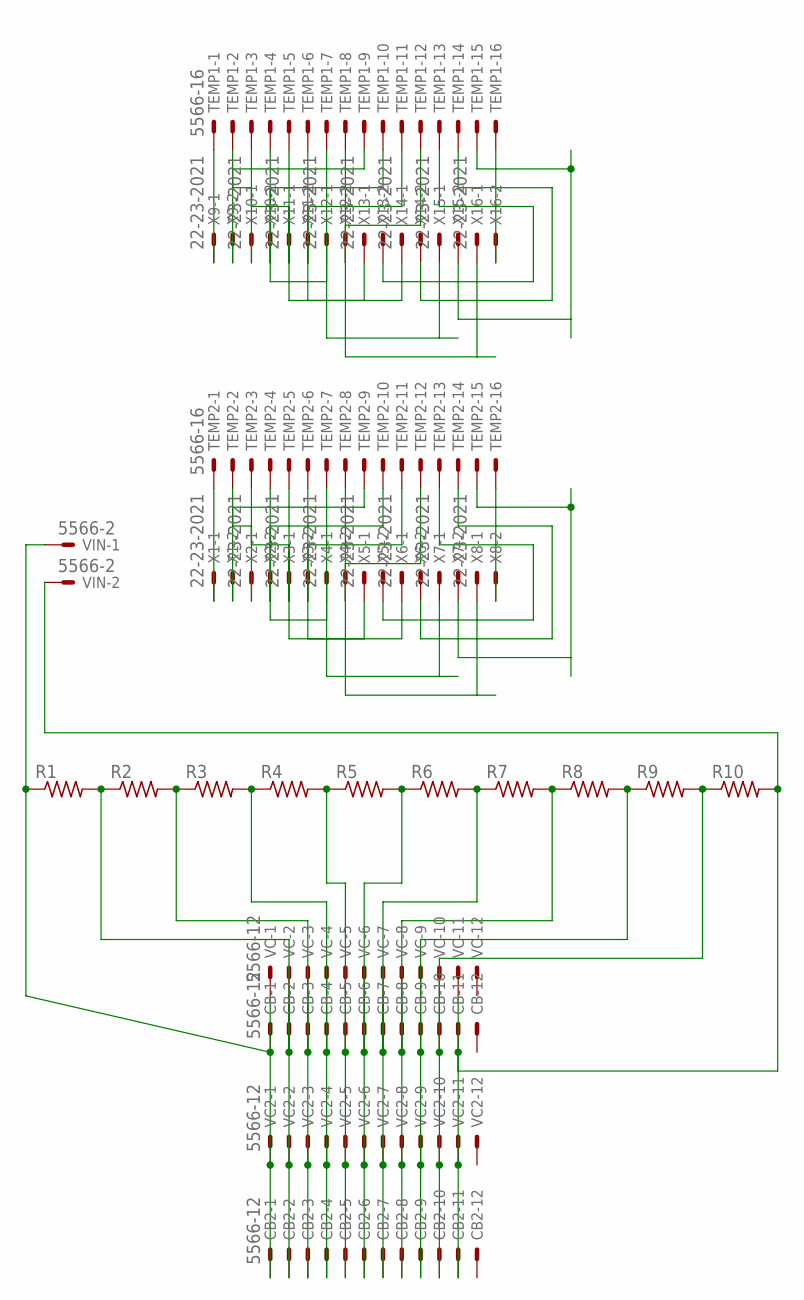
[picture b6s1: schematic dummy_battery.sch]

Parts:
CB, CB2: 5566-12
R1, R2, R3, R4, R5, R6, R7, R8, R9, R10: R-US_R0805; R0805
TEMP1, TEMP2: 5566-16
VC, VC2: 5566-12
VIN: 5566-2
X1, X2, X3, X4, X5, X6, X7, X8, X9, X10, X11, X12, X13, X14, X15, X16: 22-23-2021

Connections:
unnamed: CB.2, CB2.2, R1.2, R2.1, VC.2, VC2.2
unnamed: CB.3, CB2.3, R2.2, R3.1, VC.3, VC2.3
unnamed: CB.4, CB2.4, R3.2, R4.1, VC.4, VC2.4
unnamed: CB.5, CB2.5, R4.2, R5.1, VC.5, VC2.5
unnamed: CB.6, CB2.6, R5.2, R6.1, VC.6, VC2.6
unnamed: CB.7, CB2.7, R6.2, R7.1, VC.7, VC2.7
unnamed: CB.8, CB2.8, R7.2, R8.1, VC.8, VC2.8
unnamed: CB.9, CB2.9, R8.2, R9.1, VC.9, VC2.9
unnamed: CB.10, CB2.10, R9.2, R10.1, VC.10, VC2.10
unnamed: CB.1, CB2.1, R1.1, VC.1, VC2.1, VIN.1
unnamed: CB.11, CB2.11, R10.2, VC.11, VC2.11, VIN.2
unnamed: TEMP2.1, X1.1
unnamed: TEMP2.9, X1.2
unnamed: TEMP2.2, X2.1
unnamed: TEMP2.10, X2.2
unnamed: TEMP2.3, X3.1
unnamed: TEMP2.11, X3.2
unnamed: TEMP2.4, X4.1
unnamed: TEMP2.12, X4.2
unnamed: TEMP2.5, X5.1
unnamed: TEMP2.13, X5.2
unnamed: TEMP2.6, X6.1
unnamed: TEMP2.14, X6.2
unnamed: TEMP2.7, X7.1
unnamed: TEMP2.15, X7.2
unnamed: TEMP2.8, X8.1
unnamed: TEMP2.16, X8.2
unnamed: TEMP1.1, X9.1
unnamed: TEMP1.9, X9.2
unnamed: TEMP1.2, X10.1
unnamed: TEMP1.10, X10.2
unnamed: TEMP1.3, X11.1
unnamed: TEMP1.11, X11.2
unnamed: TEMP1.4, X12.1
unnamed: TEMP1.12, X12.2
unnamed: TEMP1.5, X13.1
unnamed: TEMP1.13, X13.2
unnamed: TEMP1.6, X14.1
unnamed: TEMP1.14, X14.2
unnamed: TEMP1.7, X15.1
unnamed: TEMP1.15, X15.2
unnamed: TEMP1.8, X16.1
unnamed: TEMP1.16, X16.2
